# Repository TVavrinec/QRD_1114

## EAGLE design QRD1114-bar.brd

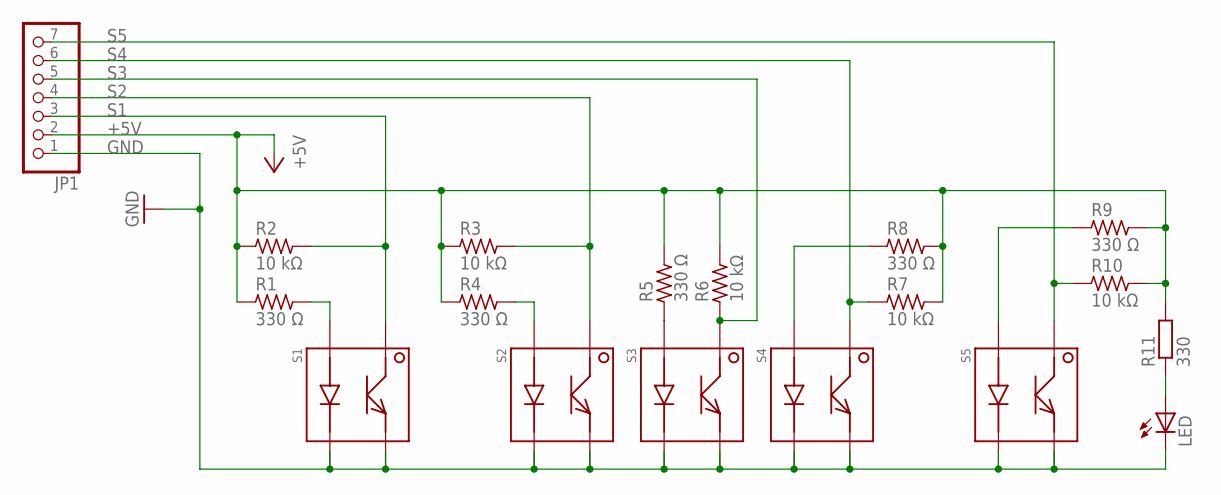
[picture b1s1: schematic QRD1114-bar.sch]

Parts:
JP1: PINHD-1X7; 1X07
LED: LEDSML0805; SML0805
R1, R4, R5, R8, R9: 330 Ω; R0603; MPN CRCW0805330RFKEA
R2, R3, R6, R7, R10: 10 kΩ; R0603
R11: 330; R0603
S1, S2, S3, S4, S5: QRD1114; MPN QRD1114

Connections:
+5V: JP1.2, R1.1, R2.1, R3.1, R4.1, R5.2, R6.2, R7.2, R8.2, R9.2, R10.2, R11.2
GND: JP1.1, LED.C, S1.P$2, S1.P$4, S2.P$2, S2.P$4, S3.P$2, S3.P$4, S4.P$2, S4.P$4, S5.P$2, S5.P$4
unnamed: R5.1, S3.P$3
unnamed: R1.2, S1.P$3
unnamed: LED.A, R11.1
unnamed: R8.1, S4.P$3
unnamed: R4.2, S2.P$3
unnamed: R9.1, S5.P$3
S1: JP1.3, R2.2, S1.P$1
S2: JP1.4, R3.2, S2.P$1
S3: JP1.5, R6.1, S3.P$1
S4: JP1.6, R7.1, S4.P$1
S5: JP1.7, R10.1, S5.P$1

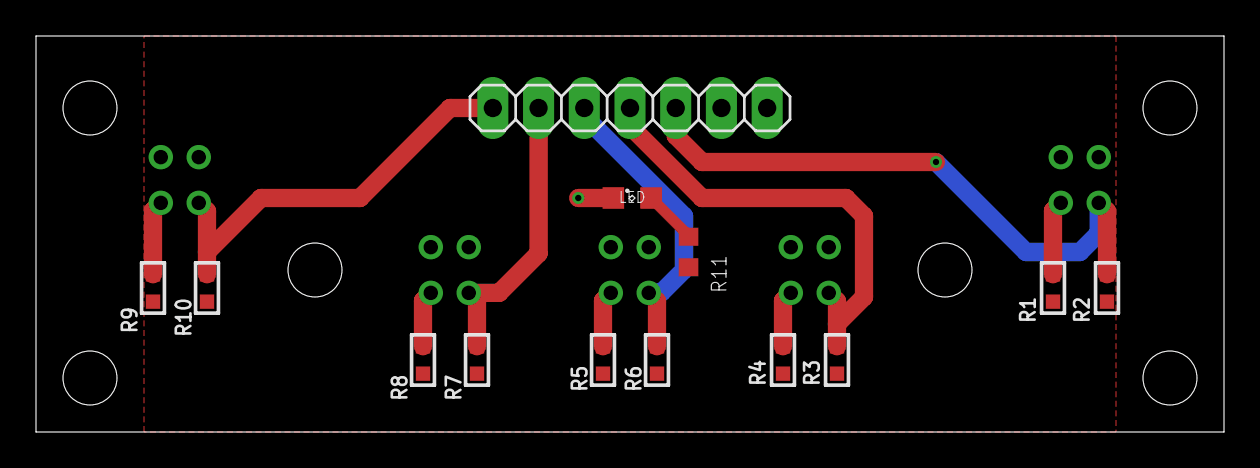
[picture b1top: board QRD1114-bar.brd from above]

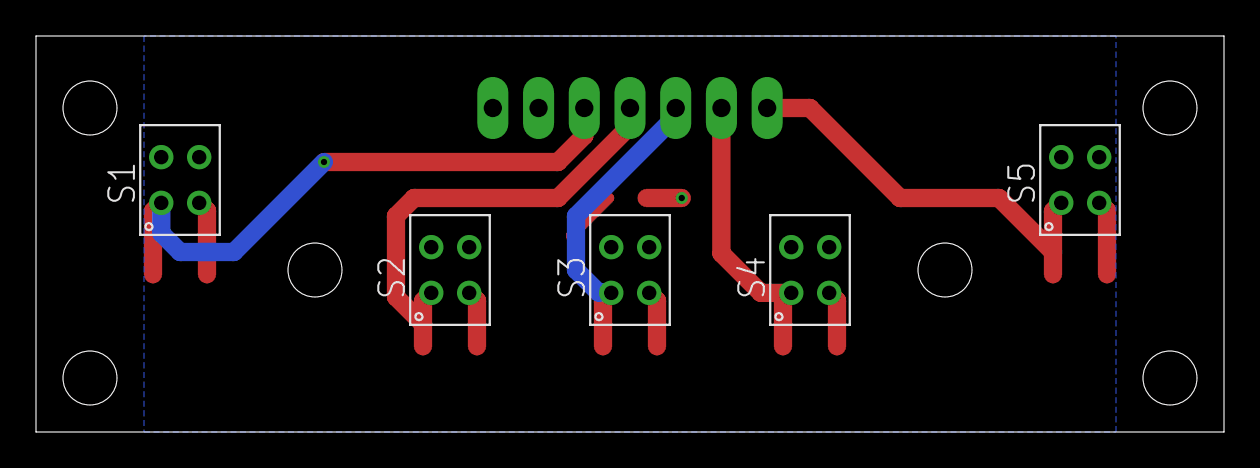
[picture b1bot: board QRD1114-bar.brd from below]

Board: 2 copper layers, 66.0 x 22.0 mm, 18 parts (5 on the bottom side), 13 nets.

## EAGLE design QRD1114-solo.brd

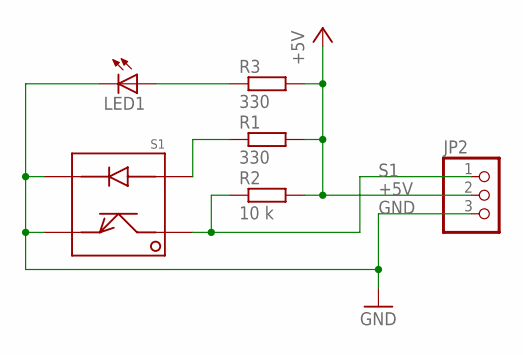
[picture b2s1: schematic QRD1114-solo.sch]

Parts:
JP2: PINHD-1X3; 1X03
LED1: LEDCHIPLED_0603; CHIPLED_0603
R1: 330; MINI_MELF-0102W
R2: 10 k; MINI_MELF-0102W
R3: 330; R0603
S1: QRD1114

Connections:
+5V: JP2.2, R1.2, R2.2, R3.2
GND: JP2.3, LED1.C, S1.P$2, S1.P$4
IL1: R1.1, S1.P$3
KL1: LED1.A, R3.1
S1: JP2.1, R2.1, S1.P$1

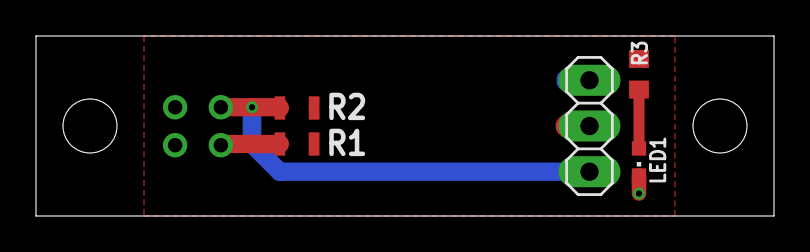
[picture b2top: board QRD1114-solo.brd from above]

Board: 2 copper layers, 41.0 x 10.0 mm, 6 parts (1 on the bottom side), 5 nets.

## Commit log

2018-06-26 Prepare PCB to manufacturing
2018-06-26 Rename project files to correspond with text on board
2018-06-26 QRD1114-bar - small change in the board for better manufacturing

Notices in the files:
parts and their libraries:
rc-master-smd: Copyright (C) 2007, Bob Starr
